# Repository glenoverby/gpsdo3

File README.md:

# gpsdo3
Improved GPS Disciplined Oscillator

This is a GPS Disciplined Oscillator for synchronizing a 10MHz osillator
with the timing signal from GPS.

This project include a printed circuit board (designed in KiCad) and software
(using Arduino).  It runs on a SparkFun SAMD21 Mini Breakout.

A full description of the project is in the 'doc' directory.

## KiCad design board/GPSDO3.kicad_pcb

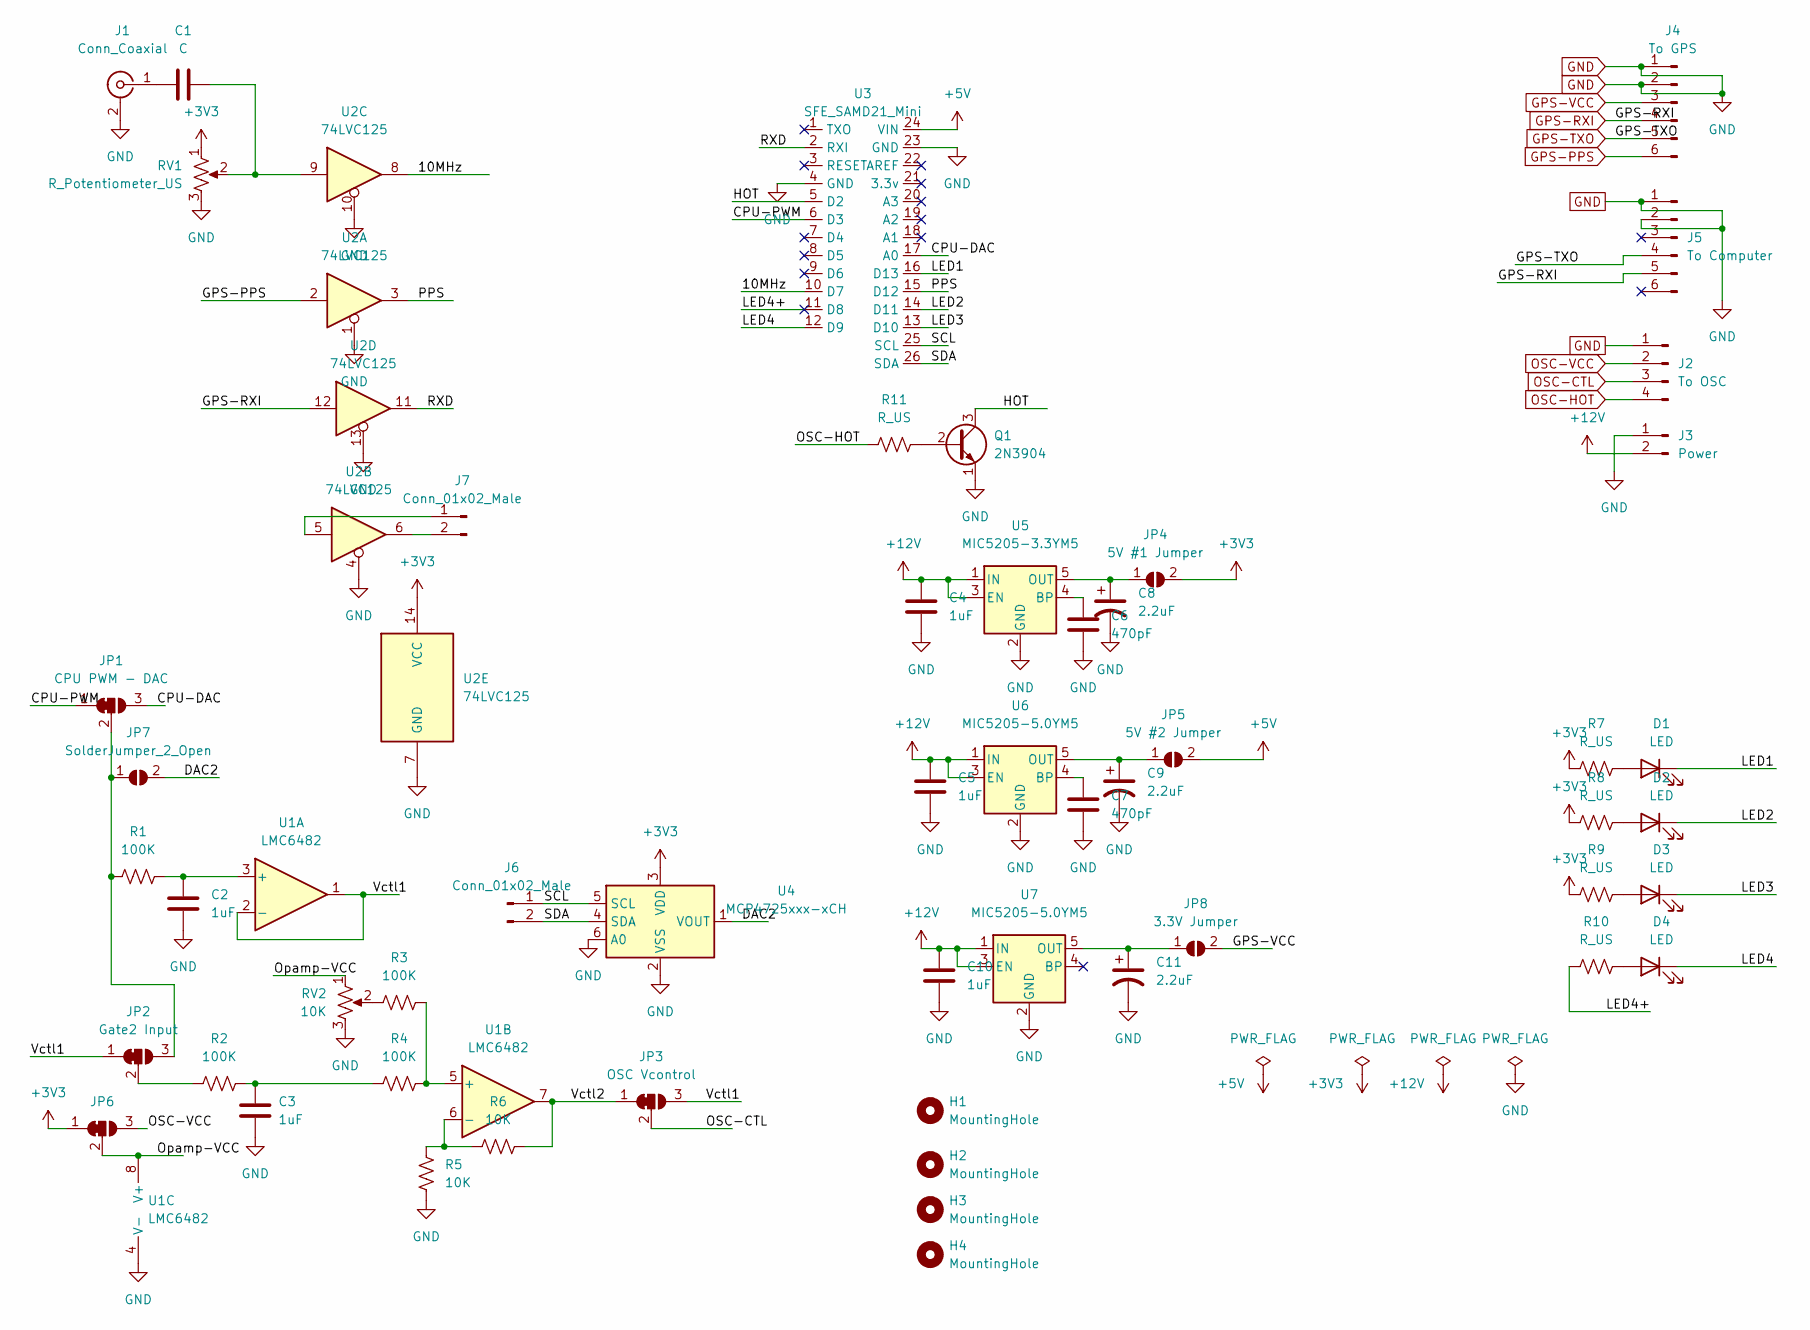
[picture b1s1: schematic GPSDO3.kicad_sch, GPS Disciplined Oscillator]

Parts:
C1: C; C_0805_2012Metric_Pad1.18x1.45mm_HandSolder
C2, C4, C5, C10: 1uF; C_0805_2012Metric_Pad1.18x1.45mm_HandSolder
C3: 1uF; C_1206_3216Metric_Pad1.33x1.80mm_HandSolder
C6, C7: 470pF; C_0805_2012Metric_Pad1.18x1.45mm_HandSolder
C8, C9, C11: 2.2uF; C_1206_3216Metric_Pad1.33x1.80mm_HandSolder
D1, D2, D3, D4: LED; LED_D5.0mm
H1, H2, H3, H4: MountingHole; MountingHole_3.2mm_M3
J1: Conn_Coaxial; PinHeader_1x02_P2.54mm_Vertical
J2: To OSC; PinHeader_1x04_P2.54mm_Vertical
J3: Power; PinHeader_1x02_P2.54mm_Vertical
J4: To GPS; PinHeader_1x06_P2.54mm_Vertical
J5: To Computer; PinHeader_1x06_P2.54mm_Vertical
J6: Conn_01x02_Male; PinHeader_1x02_P2.54mm_Vertical
J7: Conn_01x02_Male; C_0805_2012Metric_Pad1.18x1.45mm_HandSolder
JP1: CPU PWM - DAC; SolderJumper-3_P1.3mm_Open_Pad1.0x1.5mm
JP2: Gate2 Input; SolderJumper-3_P1.3mm_Open_Pad1.0x1.5mm
JP3: OSC Vcontrol; SolderJumper-3_P1.3mm_Open_Pad1.0x1.5mm
JP4: 5V #1 Jumper; SolderJumper-2_P1.3mm_Open_Pad1.0x1.5mm
JP5: 5V #2 Jumper; SolderJumper-2_P1.3mm_Open_Pad1.0x1.5mm
JP6: SolderJumper-3_P1.3mm_Open_Pad1.0x1.5mm
JP7: SolderJumper_2_Open; SolderJumper-2_P1.3mm_Open_Pad1.0x1.5mm
JP8: 3.3V Jumper; SolderJumper-2_P1.3mm_Open_Pad1.0x1.5mm
Q1: 2N3904; TO-92_Inline
R1, R2, R3, R4: 100K; R_0805_2012Metric_Pad1.20x1.40mm_HandSolder
R5, R6: 10K; R_0805_2012Metric_Pad1.20x1.40mm_HandSolder
R7, R8, R9, R10, R11: R_US; R_0805_2012Metric_Pad1.20x1.40mm_HandSolder
RV1: R_Potentiometer_US; Potentiometer_ACP_CA6-H2,5_Horizontal
RV2: 10K; Potentiometer_ACP_CA6-H2,5_Horizontal
U1: LMC6482; SOIC-8_5.23x5.23mm_P1.27mm
U2: 74LVC125; SOIC-14_3.9x8.7mm_P1.27mm
U3: SFE_SAMD21_Mini; SFE SAMD21 Mini
U4: MCP4725xxx-xCH; SOT-23-6
U5: MIC5205-3.3YM5; SOT-23-5
U6, U7: MIC5205-5.0YM5; SOT-23-5

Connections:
+3V3: JP4.2 (B), JP6.1 (A), R7.2, R8.2, R9.2, RV1.1, U2.14 (VCC), U4.3 (VDD)
+5V: JP5.2 (B), U3.24 (VIN)
+12V: C4.1, C5.1, C10.1, J3.2, U5.1 (IN), U5.3 (EN), U6.1 (IN), U6.3 (EN), U7.1 (IN), U7.3 (EN)
/10MHz: U2.8, U3.10 (D7)
/CPU-DAC: JP1.3 (B), U3.17 (A0)
/CPU-PWM: JP1.1 (A), U3.6 (D3)
/DAC2: JP7.2 (B), U4.1 (VOUT)
/HOT: Q1.3 (C), U3.5 (D2)
/LED1: D1.1 (K), U3.16 (D13)
/LED2: D2.1 (K), U3.14 (D11)
/LED3: D3.1 (K), U3.13 (D10)
/LED4: D4.1 (K), U3.12 (D9)
/LED4+: R10.2, U3.11 (D8)
/Opamp-VCC: JP6.2 (C), RV2.1, U1.8 (V+)
/PPS: U2.3, U3.15 (D12)
/RXD: U2.11, U3.2 (RXI)
/SCL: J6.1, U3.25 (SCL), U4.5 (SCL)
/SDA: J6.2, U3.26 (SDA), U4.4 (SDA)
/Vctl1: JP2.1 (A), JP3.3 (B), U1.1, U1.2 (-)
/Vctl2: JP3.1 (A), R6.2, U1.7
GND: C2.2, C3.2, C4.2, C5.2, C6.2, C7.2, C8.2, C9.2, C10.2, C11.2, J1.2 (Ext), J2.1, J3.1, J4.1, J4.2, J5.1, J5.2, Q1.1 (E), R5.2, RV1.3, RV2.3, U1.4 (V-), U2.1, U2.4, U2.7 (GND), U2.10, U2.13, U3.4 (GND), U3.23 (GND), U4.2 (VSS), U4.6 (A0), U5.2 (GND), U6.2 (GND), U7.2 (GND)
GPS-PPS: J4.6, U2.2
GPS-RXI: J4.4, J5.5, U2.12
GPS-TXO: J4.5, J5.4
GPS-VCC: J4.3, JP8.2 (B)
unnamed: C1.1, RV1.2, U2.9
unnamed: C3.1, R2.1, R4.2
unnamed: D1.2 (A), R7.1
unnamed: D2.2 (A), R8.1
unnamed: D3.2 (A), R9.1
unnamed: D4.2 (A), R10.1
unnamed: C1.2, J1.1 (In)
unnamed: J7.1, U2.5
unnamed: J7.2, U2.6
unnamed: JP1.2 (C), JP2.3 (B), JP7.1 (A), R1.2
unnamed: JP2.2 (C), R2.2
unnamed: C8.1, JP4.1 (A), U5.5 (OUT)
unnamed: C9.1, JP5.1 (A), U6.5 (OUT)
unnamed: C11.1, JP8.1 (A), U7.5 (OUT)
unnamed: Q1.2 (B), R11.1
unnamed: R3.2, RV2.2
unnamed: C2.1, R1.1, U1.3 (+)
unnamed: R3.1, R4.1, U1.5 (+)
unnamed: R5.1, R6.1, U1.6 (-)
unnamed: C6.1, U5.4 (BP)
unnamed: C7.1, U6.4 (BP)
OSC-CTL: J2.3, JP3.2 (C)
OSC-HOT: J2.4, R11.2
OSC-VCC: J2.2, JP6.3 (B)

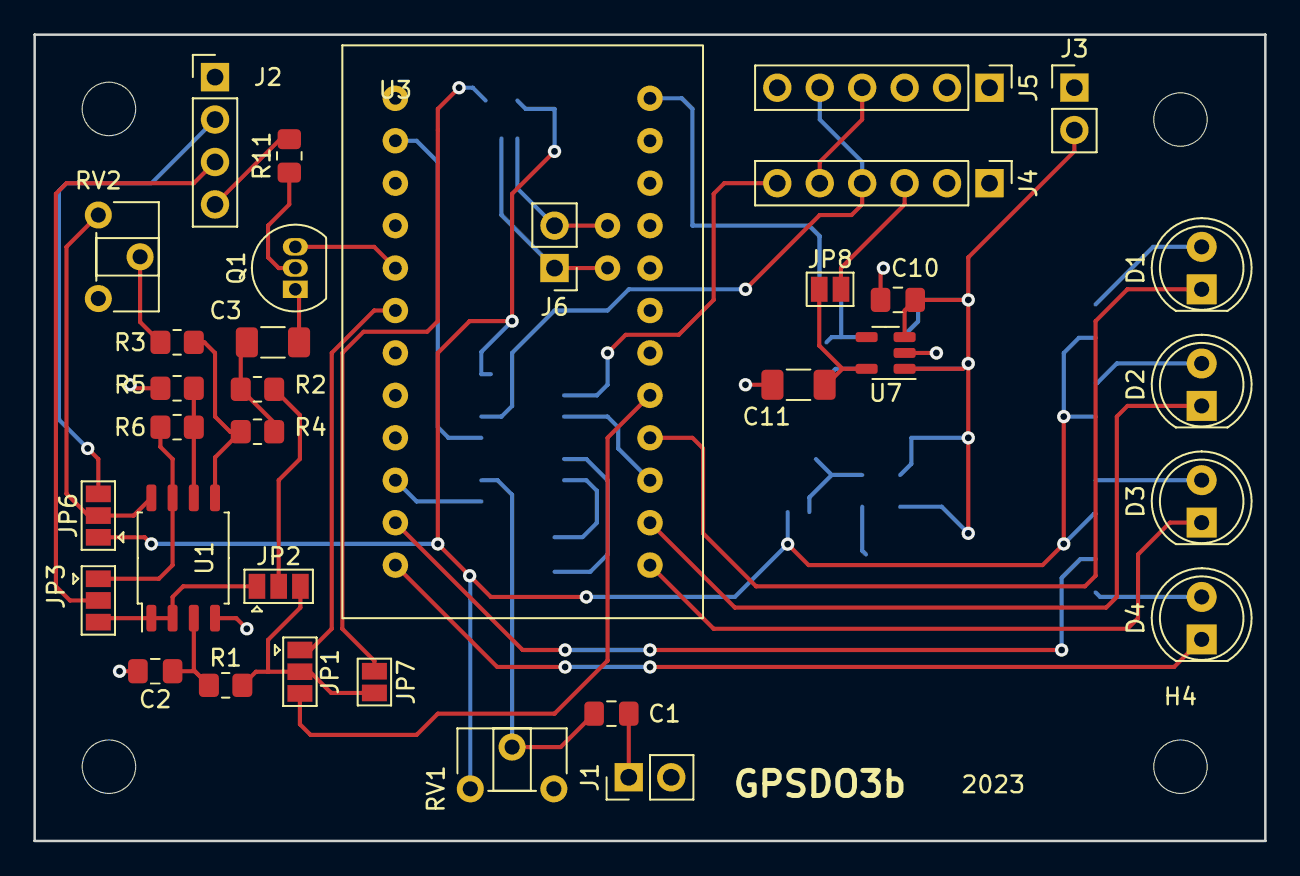
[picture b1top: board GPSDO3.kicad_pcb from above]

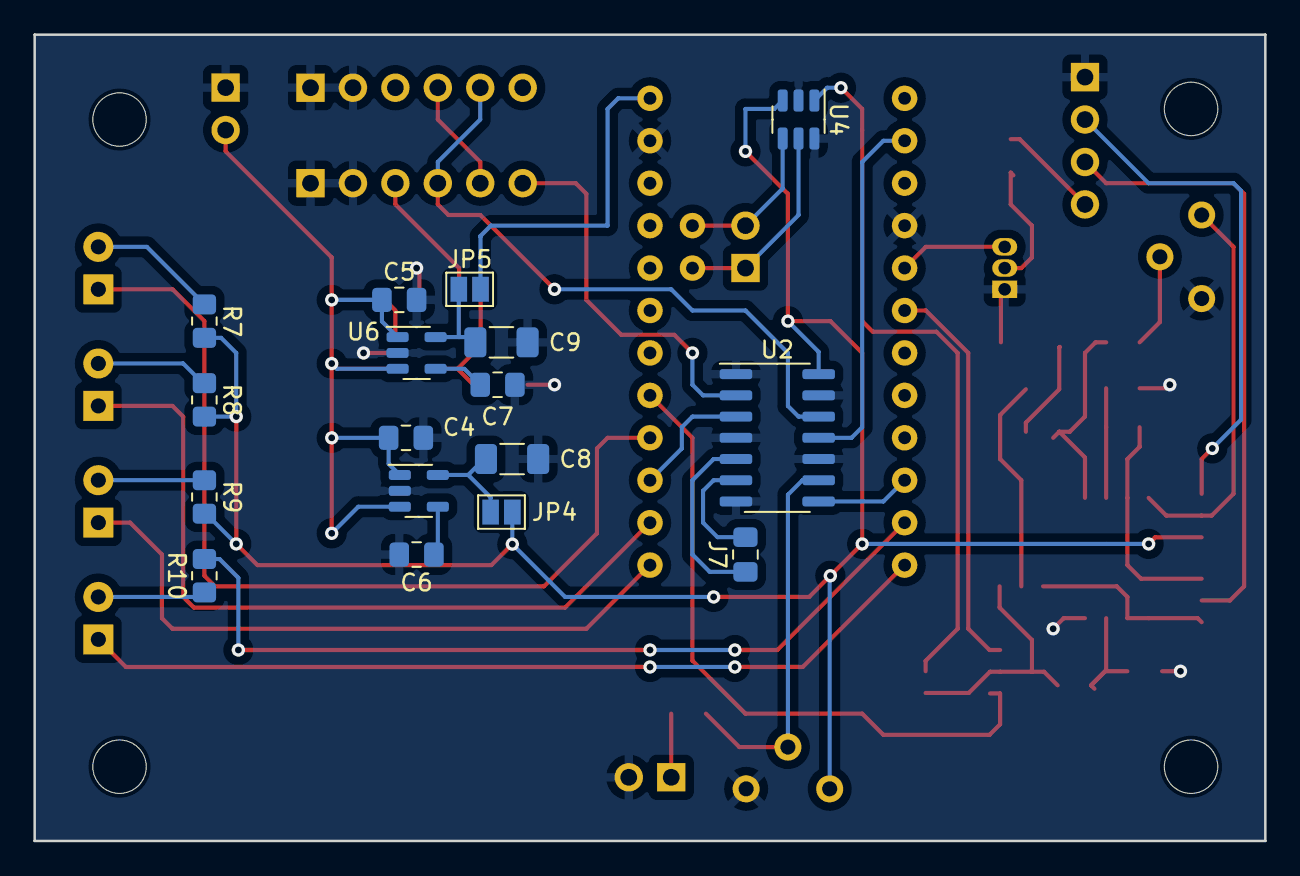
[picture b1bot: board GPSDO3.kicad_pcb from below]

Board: 2 copper layers, 73.7 x 48.3 mm, 55 parts (17 on the bottom side), 49 nets.

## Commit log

2024-12-03 Import designs, source, doc, etc.
    Brought all the components of the project together in one GIT
    repository.
